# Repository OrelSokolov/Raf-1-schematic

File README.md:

# Raf-1 Schematic

Schematic files for Raf-1 robot.

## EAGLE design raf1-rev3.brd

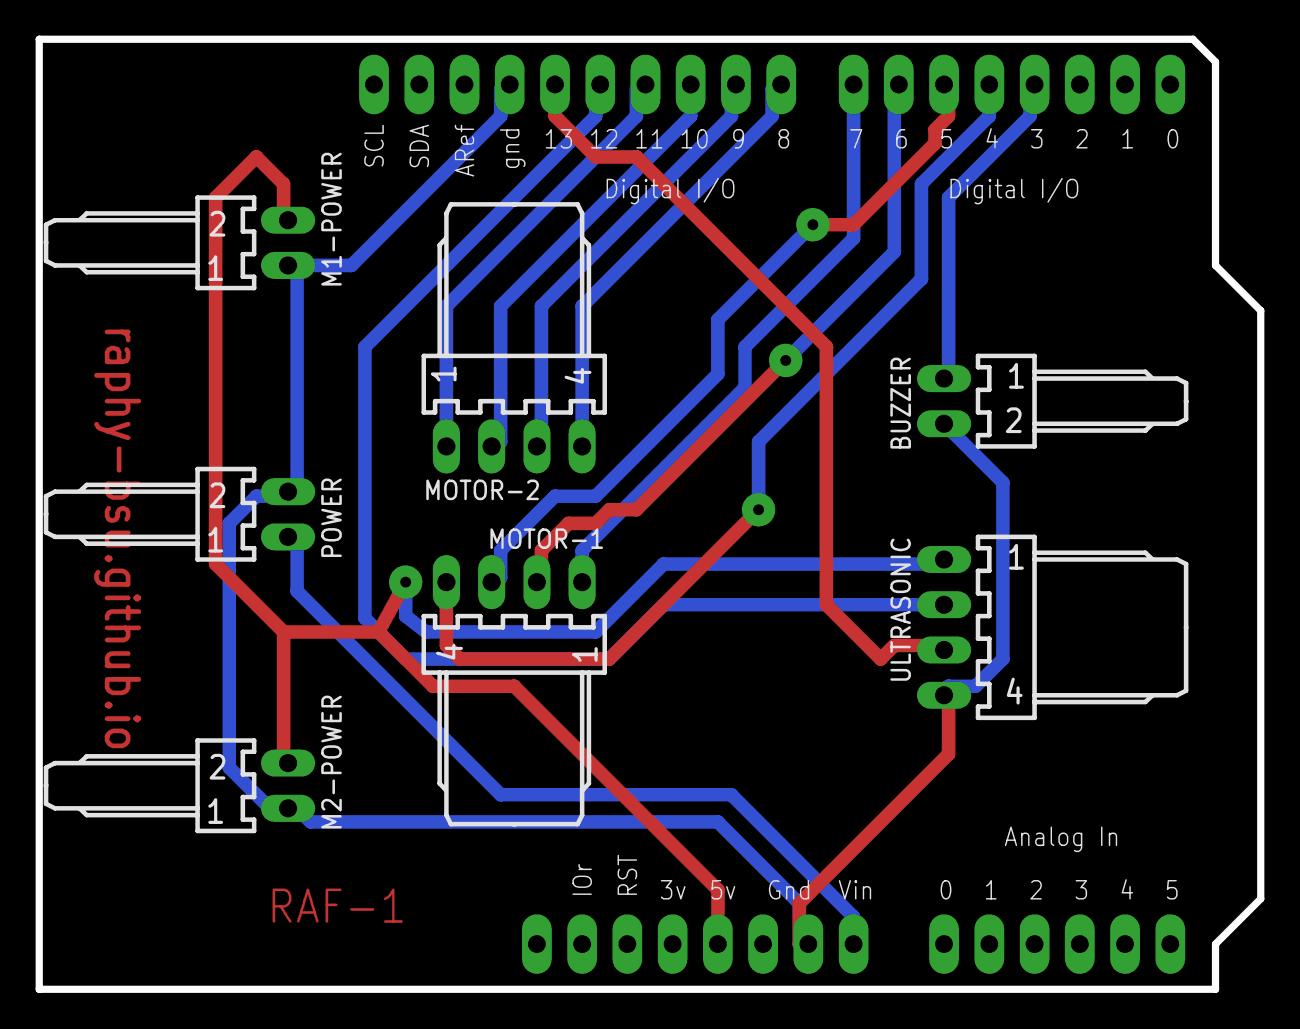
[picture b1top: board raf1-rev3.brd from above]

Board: 2 copper layers, 68.6 x 53.3 mm, 8 parts (0 on the bottom side), 14 nets.

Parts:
BUZZER: 22-05-7028-02; 7395-02
M1-POWER, M2-POWER: 22-05-7028-02; 7395-02
MOTOR-1, MOTOR-2: 22-05-7048-04; 7395-04
POWER: 22-05-7028-02; 7395-02
U1: ARDUINOR3-BPLACE
ULTRASONIC: 22-05-7048-04; 7395-04

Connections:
5V: M1-POWER.2, M2-POWER.2, U1.5V
BZR: BUZZER.1, U1.D3
ECHO: U1.D13, ULTRASONIC.3
GND: BUZZER.2, M1-POWER.1, M2-POWER.1, POWER.2, U1.GND, U1.GND1, ULTRASONIC.4
MOTOR1-1: MOTOR-1.1, U1.D7
MOTOR1-2: MOTOR-1.2, U1.D6
MOTOR1-3: MOTOR-1.3, U1.D5
MOTOR1-4: MOTOR-1.4, U1.D4
MOTOR2-1: MOTOR-2.1, U1.D11
MOTOR2-2: MOTOR-2.2, U1.D10
MOTOR2-3: MOTOR-2.3, U1.D9
MOTOR2-4: MOTOR-2.4, U1.D8
TRIG: U1.D12, ULTRASONIC.2
VCC: POWER.1, U1.VIN

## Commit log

2014-12-03 Add project files
